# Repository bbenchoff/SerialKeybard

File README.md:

# Serial Keyboard

It's a keyboard that transmits serial. Or it's a 256-key keyboard, using 18 keys. Something like that. The main thing is that it transmits any serial byte.

## Notice

This repo contains a few files, but is mostly geared towards an unoptimized build with the internal structure consisting of five(!) different PCBs. The SerialKeyboard.brd is just a 18-key keyboard with diodes. The DisplayCarrier.brd is an interposer between the display and Motherboard.brd, which is the only thing with active electronics. There's also an Arduino in there and the front panel, which makes for a grand total of five different PCBs in this project.

I have started work on a simplified version, MasterBoard.brd, which would combine this all into one single circuit board. This work is not completed.

If someone can find me a source of 2U 'Transmit' keycaps, I'll get right on that.

Oh yeah, I noticed this repo was named 'SerialKeybard', but it's too late to fix it now.

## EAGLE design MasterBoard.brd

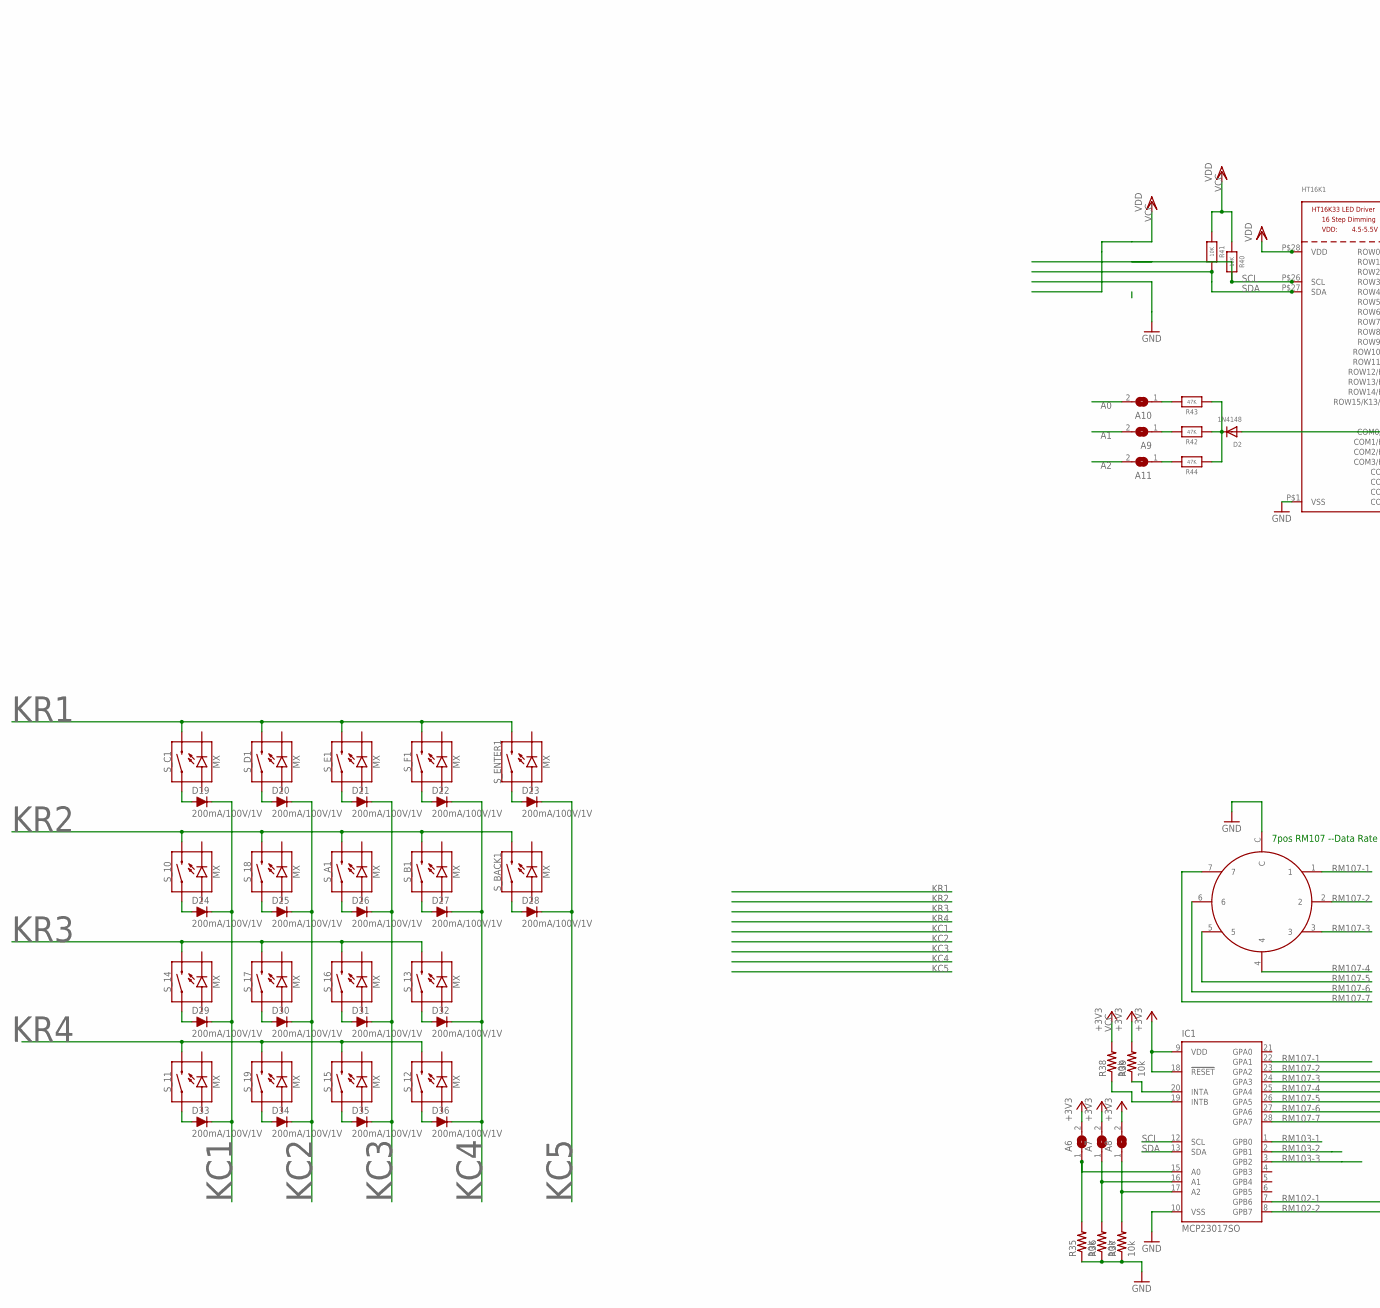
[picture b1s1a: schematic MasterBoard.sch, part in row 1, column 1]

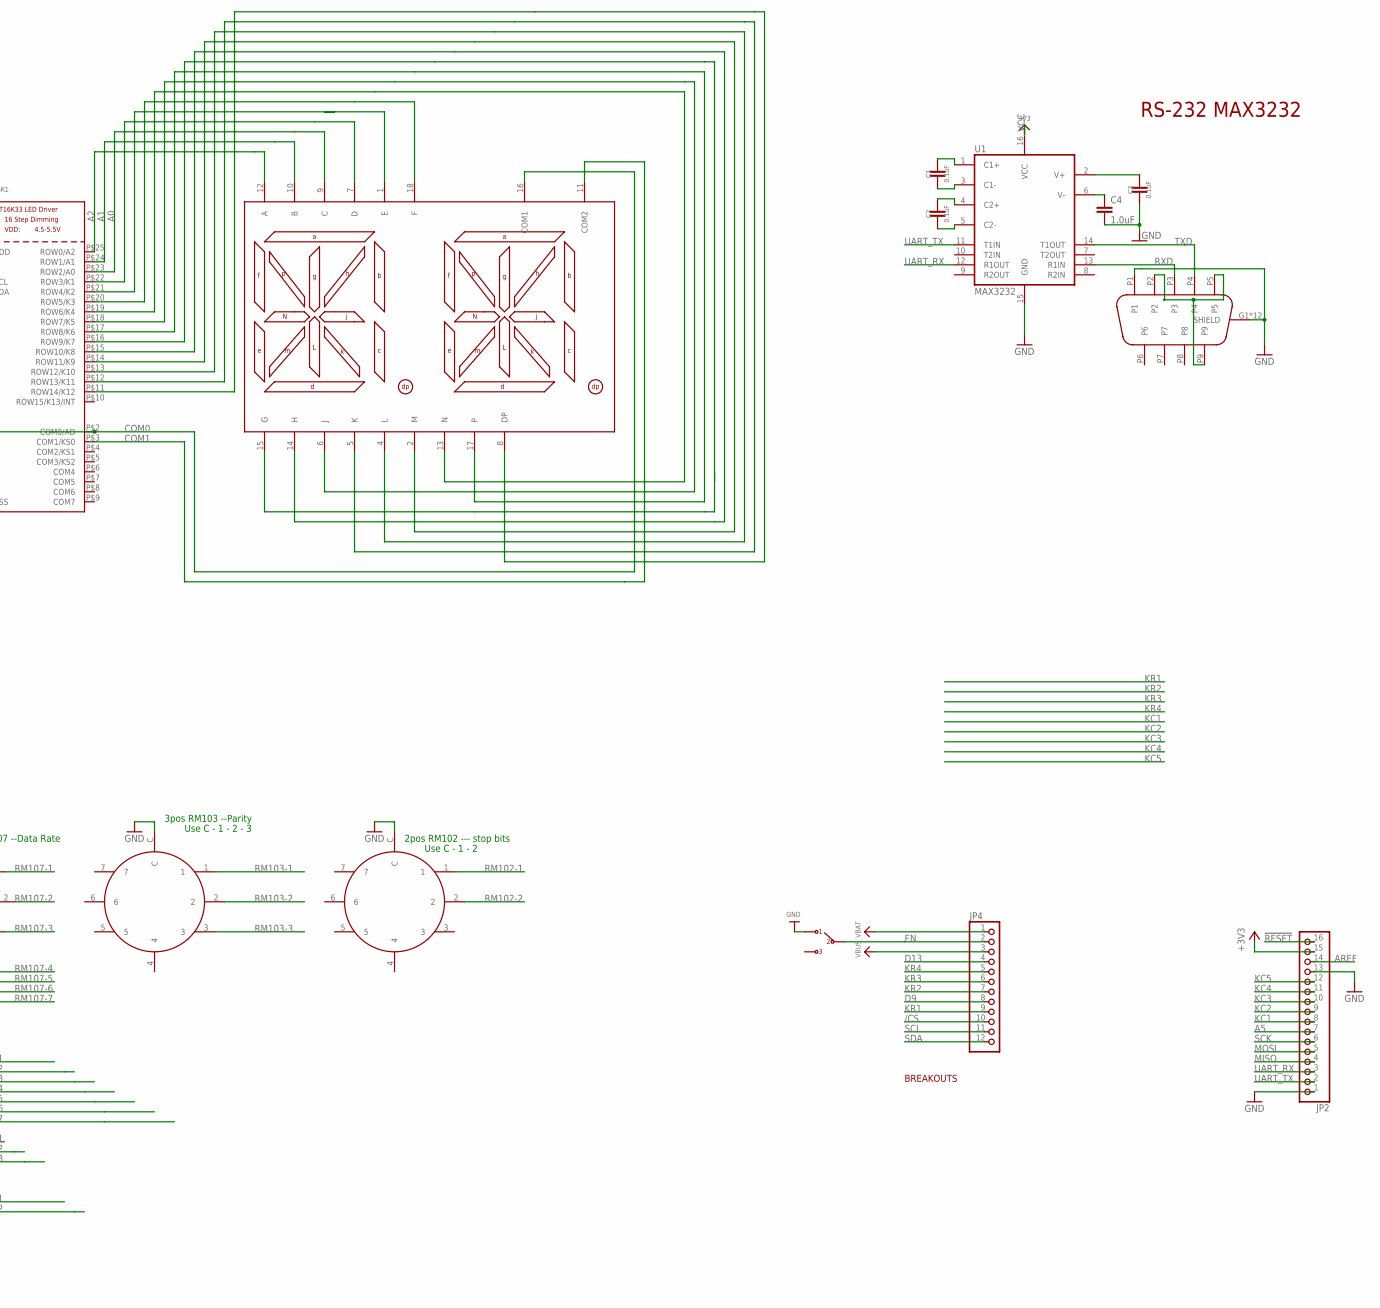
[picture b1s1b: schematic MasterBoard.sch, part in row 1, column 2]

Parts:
A6, A7, A8: SJ
A9, A10, A11: SOLDERJUMPERREFLOW_NOPASTE; SOLDERJUMPER_REFLOW_NOPASTE
C1, C2, C3: 0.1uF; 0805
C4: 1.0uF; 0805
D2: 1N4148; SOD-323F
D19, D20, D21, D22, D23, D24, D25, D26, D27, D28, D29, D30, D31, D32, D33, D34, D35, D36: 200mA/100V/1V; DIODE-1N4148
DE9FEMALE1: EDGEMOUNTDE9; DE09S065TLF
HT16K1: HT16K33_SOP28_SKINNY; SOP28_300MIL_SKINNY
IC1: MCP23017SO; SO28W
JP2: HEADER-1X16ROUND; 1X16_ROUND
JP4: HEADER-1X12; 1X12_ROUND
R35, R36, R37, R38, R39: 10k; M0805
R40, R41: 10K; 0805-NO
R42, R43, R44: 47K; 0805-NO
S_10, S_11, S_12, S_13, S_14, S_15, S_16, S_17, S_18, S_19: MX; CHERRY-MX-LED
S_A1: MX; CHERRY-MX-LED
S_B1: MX; CHERRY-MX-LED
S_BACK1: MX; CHERRY-MX-LED
S_C1: MX; CHERRY-MX-LED
S_D1: MX; CHERRY-MX-LED
S_E1: MX; CHERRY-MX-LED
S_ENTER1: MX; CHERRY-MX-LED
S_F1: MX; CHERRY-MX-LED
U1: MAX3232; SO16
U$11: BIG14SEG; HDSP
U$12, U$17, U$18: RM107772BCB
U$15: OS102011MA1QN1

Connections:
!RESET: JP2.16
/CS: JP4.10
A0: A10.2, HT16K1.P$23 (ROW2/A0), U$11.9 (C)
A1: A9.2, HT16K1.P$24 (ROW1/A1), U$11.10 (B)
A2: A11.2, HT16K1.P$25 (ROW0/A2), U$11.12 (A)
A5: JP2.7
AREF: JP2.14
COM0: D2.A, HT16K1.P$2 (COM0/AD), U$11.16 (COM1)
COM1: HT16K1.P$3 (COM1/KS0), U$11.11 (COM2)
D9: JP4.8
D13: JP4.4
EN: JP4.2, U$15.P$2
GND: C3.2, C4.2, DE9FEMALE1.G1 (SHIELD), DE9FEMALE1.G2 (SHIELD), DE9FEMALE1.G3 (SHIELD), DE9FEMALE1.G4 (SHIELD), DE9FEMALE1.G5 (SHIELD), DE9FEMALE1.G6 (SHIELD), DE9FEMALE1.G7 (SHIELD), DE9FEMALE1.G8 (SHIELD), DE9FEMALE1.G9 (SHIELD), DE9FEMALE1.G10 (SHIELD), DE9FEMALE1.G11 (SHIELD), DE9FEMALE1.G12 (SHIELD), DE9FEMALE1.P1, HT16K1.P$1 (VSS), IC1.10 (VSS), JP2.1, JP2.13, R35.1, R36.1, R37.1, U1.15 (GND), U$12.C, U$15.P$1, U$17.C, U$18.C
KC1: D19.C, D24.C, D29.C, D33.C, JP2.8
KC2: D20.C, D25.C, D30.C, D34.C, JP2.9
KC3: D21.C, D26.C, D31.C, D35.C, JP2.10
KC4: D22.C, D27.C, D32.C, D36.C, JP2.11
KC5: D23.C, D28.C, JP2.12
KR1: JP4.9, S_C1.S2 (2), S_D1.S2 (2), S_E1.S2 (2), S_ENTER1.S2 (2), S_F1.S2 (2)
KR2: JP4.7, S_10.S2 (2), S_18.S2 (2), S_A1.S2 (2), S_B1.S2 (2), S_BACK1.S2 (2)
KR3: JP4.6, S_13.S2 (2), S_14.S2 (2), S_16.S2 (2), S_17.S2 (2)
KR4: JP4.5, S_11.S2 (2), S_12.S2 (2), S_15.S2 (2), S_19.S2 (2)
MISO: JP2.4
MOSI: JP2.5
unnamed: D33.A, S_11.S1 (1)
unnamed: D34.A, S_19.S1 (1)
unnamed: D35.A, S_15.S1 (1)
unnamed: D36.A, S_12.S1 (1)
unnamed: D29.A, S_14.S1 (1)
unnamed: D30.A, S_17.S1 (1)
unnamed: D31.A, S_16.S1 (1)
unnamed: D32.A, S_13.S1 (1)
unnamed: D24.A, S_10.S1 (1)
unnamed: D25.A, S_18.S1 (1)
unnamed: D26.A, S_A1.S1 (1)
unnamed: D27.A, S_B1.S1 (1)
unnamed: D28.A, S_BACK1.S1 (1)
unnamed: D23.A, S_ENTER1.S1 (1)
unnamed: D22.A, S_F1.S1 (1)
unnamed: D21.A, S_E1.S1 (1)
unnamed: D20.A, S_D1.S1 (1)
unnamed: D19.A, S_C1.S1 (1)
unnamed: C1.2, U1.3 (C1-)
unnamed: C1.1, U1.1 (C1+)
unnamed: C2.1, U1.4 (C2+)
unnamed: C2.2, U1.5 (C2-)
unnamed: C3.1, U1.2 (V+)
unnamed: C4.1, U1.6 (V-)
unnamed: DE9FEMALE1.P2, DE9FEMALE1.P5, DE9FEMALE1.P9
unnamed: A6.1, IC1.15 (A0), R35.2
unnamed: A7.1, IC1.16 (A1), R36.2
unnamed: A8.1, IC1.17 (A2), R37.2
unnamed: IC1.19 (INTB), R38.1
unnamed: IC1.20 (INTA), R39.1
unnamed: A9.1, R42.2
unnamed: A10.1, R43.2
unnamed: HT16K1.P$22 (ROW3/K1), U$11.7 (D)
unnamed: HT16K1.P$21 (ROW4/K2), U$11.1 (E)
unnamed: HT16K1.P$20 (ROW5/K3), U$11.18 (F)
unnamed: HT16K1.P$19 (ROW6/K4), U$11.13 (N)
unnamed: HT16K1.P$18 (ROW7/K5), U$11.6 (J)
unnamed: D2.C, R42.1, R43.1, R44.1
unnamed: A11.1, R44.2
unnamed: HT16K1.P$17 (ROW8/K6), U$11.17
unnamed: HT16K1.P$16 (ROW9/K7), U$11.15 (G)
unnamed: HT16K1.P$15 (ROW10/K8), U$11.14 (H)
unnamed: HT16K1.P$14 (ROW11/K9), U$11.2 (M)
unnamed: HT16K1.P$13 (ROW12/K10), U$11.4 (L)
unnamed: HT16K1.P$12 (ROW13/K11), U$11.5 (K)
unnamed: HT16K1.P$11 (ROW14/K12), U$11.8 (DP)
RM102-1: IC1.7 (GPB6), U$18.1
RM102-2: IC1.8 (GPB7), U$18.2
RM103-1: IC1.1 (GPB0), U$17.1
RM103-2: IC1.2 (GPB1), U$17.2
RM103-3: IC1.3 (GPB2), U$17.3
RM107-1: IC1.22 (GPA1), U$12.1
RM107-2: IC1.23 (GPA2), U$12.2
RM107-3: IC1.24 (GPA3), U$12.3
RM107-4: IC1.25 (GPA4), U$12.4
RM107-5: IC1.26 (GPA5), U$12.5
RM107-6: IC1.27 (GPA6), U$12.6
RM107-7: IC1.28 (GPA7), U$12.7
RXD: DE9FEMALE1.P3, U1.13 (R1IN)
SCK: JP2.6
SCL: HT16K1.P$26 (SCL), IC1.12 (SCL), JP4.11, R40.2
SDA: HT16K1.P$27 (SDA), IC1.13 (SDA), JP4.12, R41.2
TXD: DE9FEMALE1.P4, U1.14 (T1OUT)
UART_RX: JP2.3, U1.12 (R1OUT)
UART_TX: JP2.2, U1.11 (T1IN)
VBAT: JP4.1
VBUS: JP4.3
VCC: A6.2, A7.2, A8.2, HT16K1.P$28 (VDD), IC1.9 (VDD), IC1.18 (!RESET), JP2.15, R38.2, R39.2, R40.1, R41.1, U1.16 (VCC)

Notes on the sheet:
RS-232 MAX3232
7pos RM107 --Data Rate
3pos RM103 --Parity
Use C - 1 - 2 - 3
2pos RM102 --- stop bits
Use C - 1 - 2
BREAKOUTS

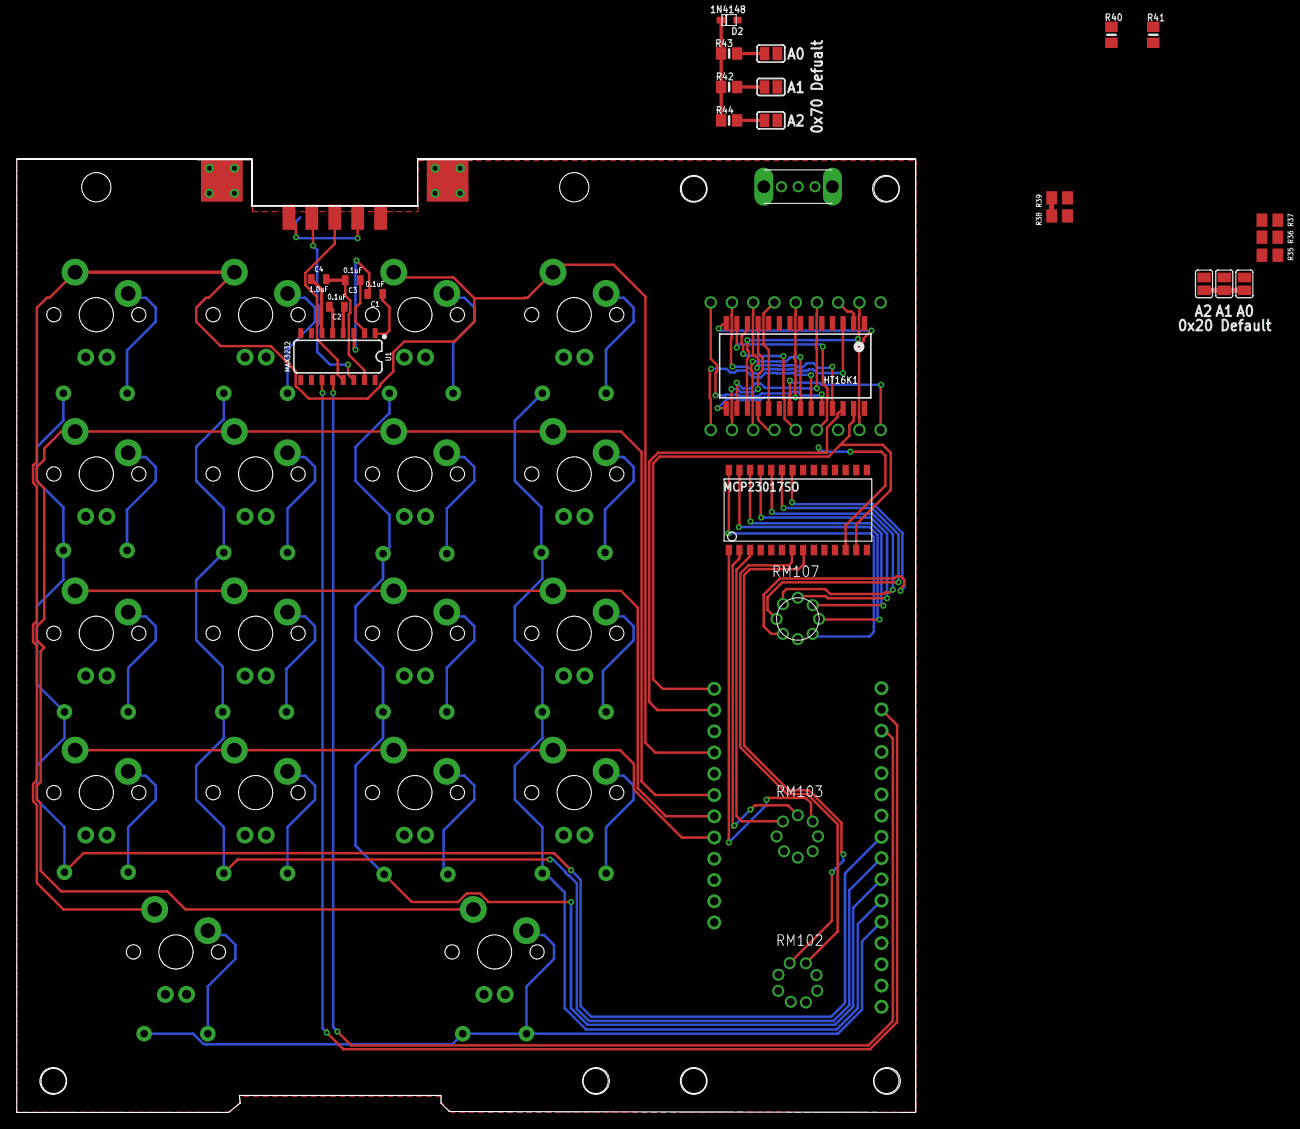
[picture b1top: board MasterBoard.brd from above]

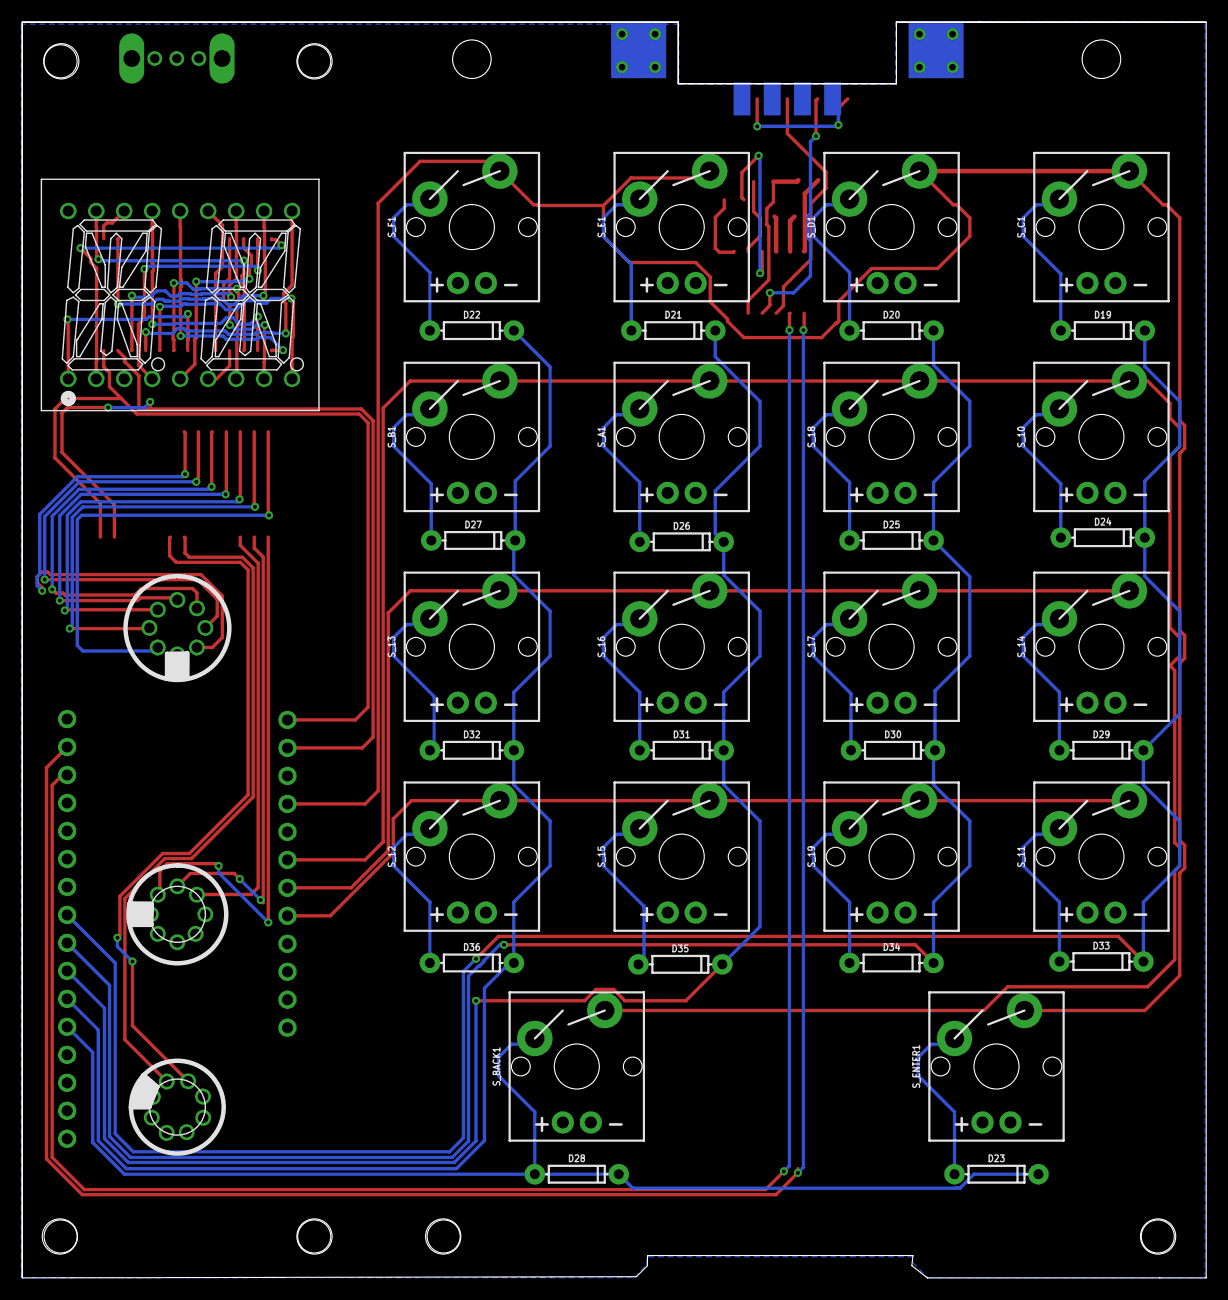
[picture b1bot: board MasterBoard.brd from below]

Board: 2 copper layers, 107.5 x 114.0 mm, 68 parts (39 on the bottom side), 81 nets.

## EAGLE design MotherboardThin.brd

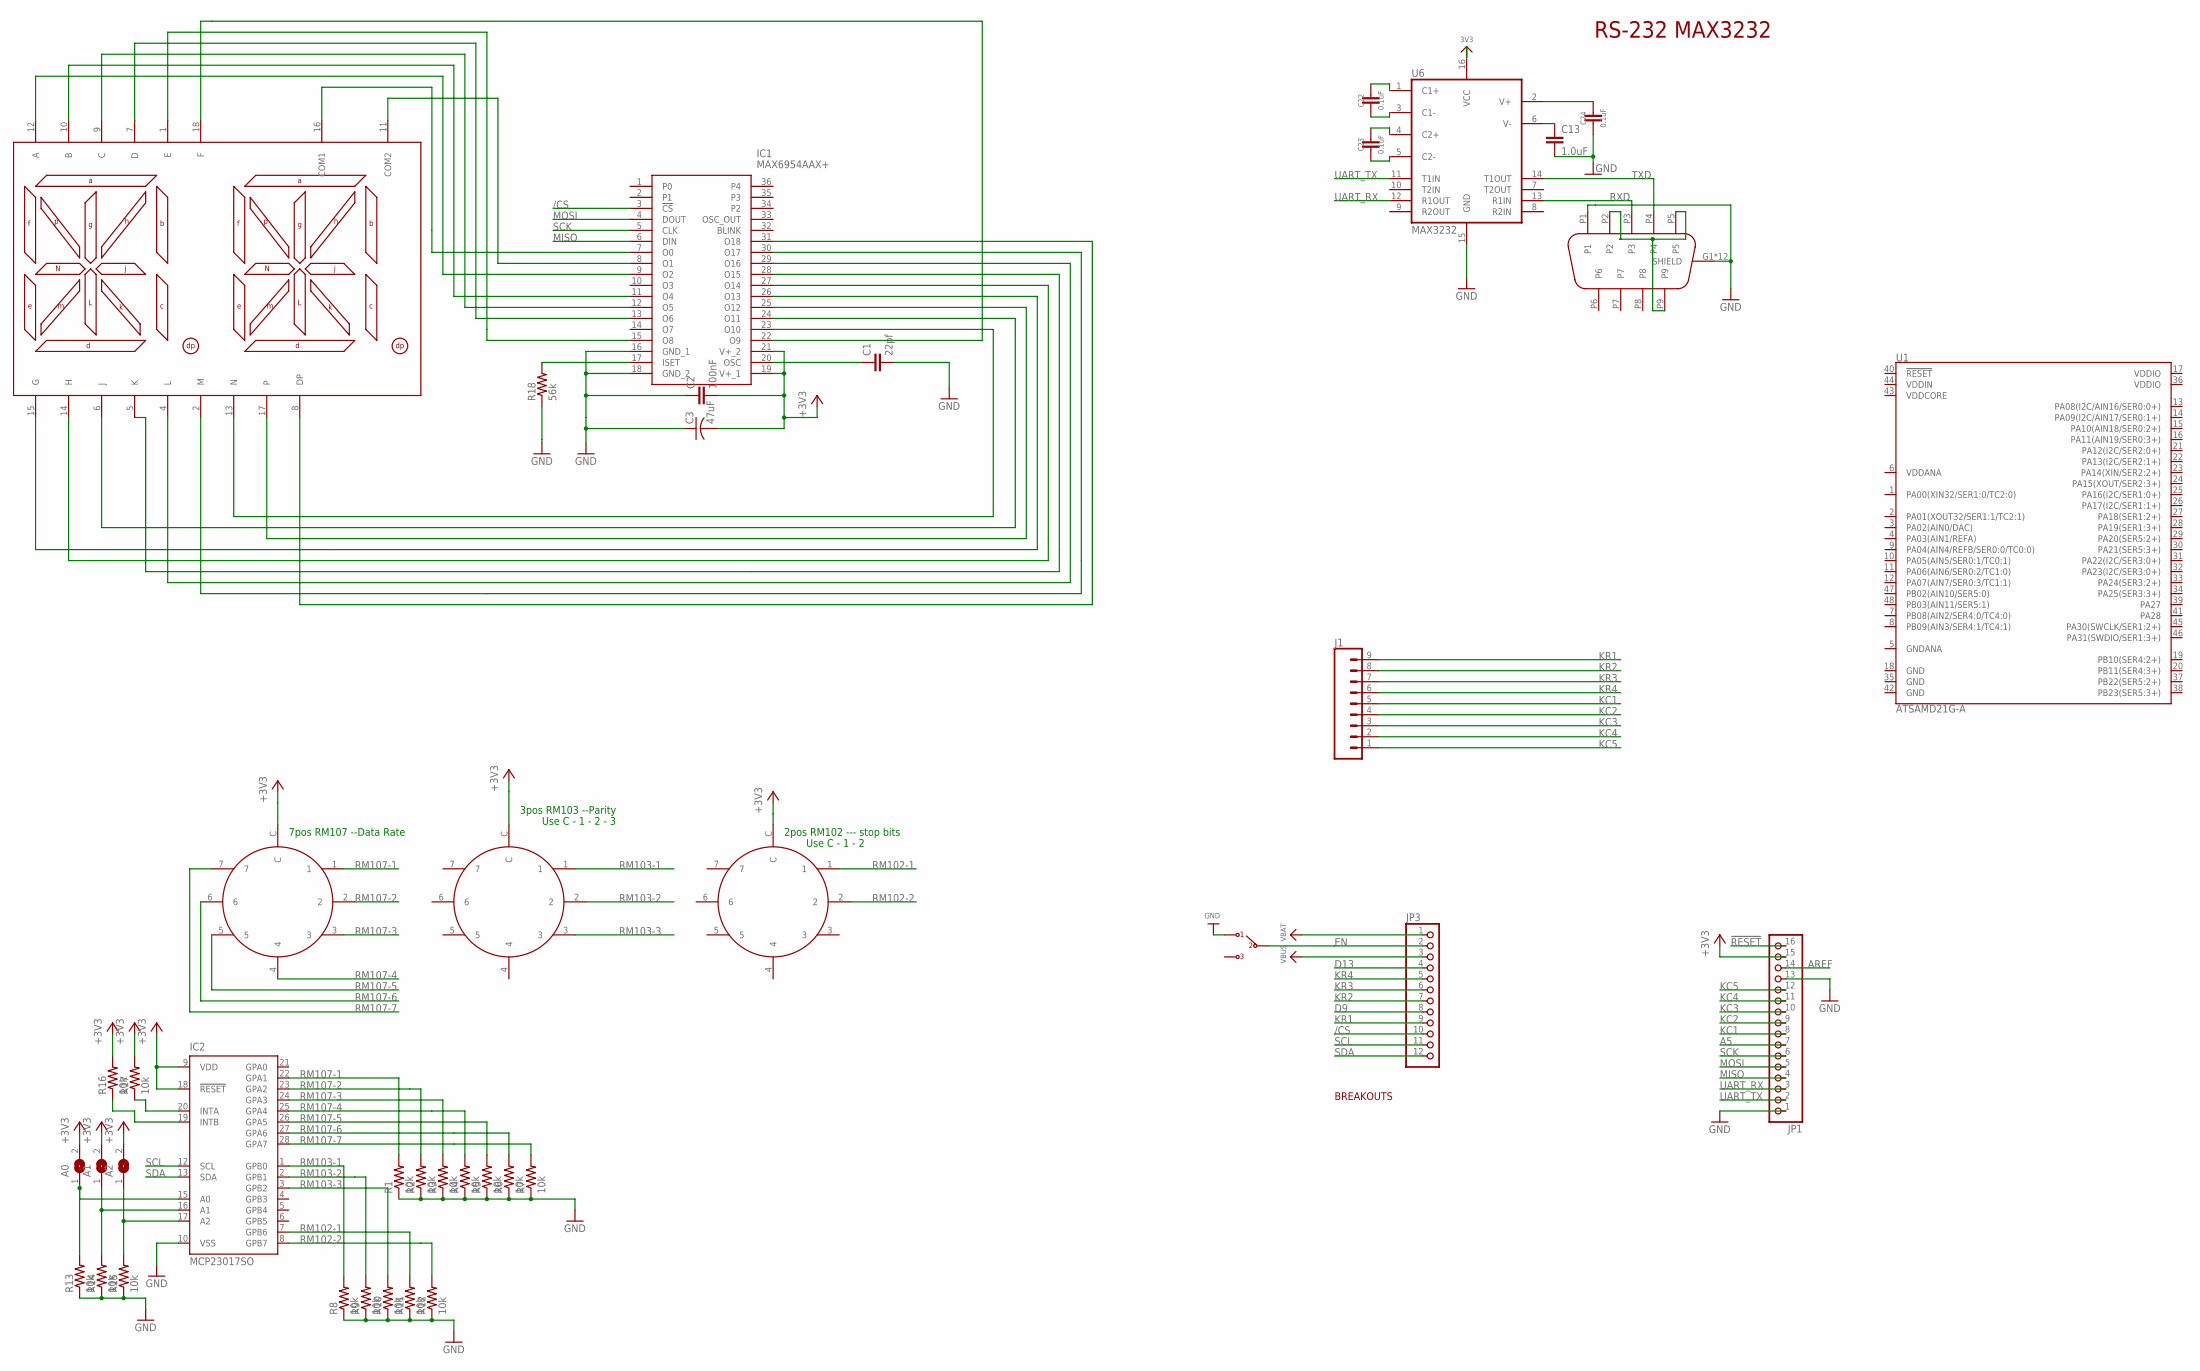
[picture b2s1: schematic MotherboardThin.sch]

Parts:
A0, A1, A2: SJ
C1: 22pf; 0805
C2: 100nF; 0805
C3: 47uF; C1206
C13: 1.0uF; 0805
C22, C23, C24: 0.1uF; 0805
DE9FEMALE: EDGEMOUNTDE9; DE09S065TLF
IC1: MAX6954AAX+; SOP80P1030X264-36N
IC2: MCP23017SO; SO28W
J1: CONN_09; 1X09
JP1: HEADER-1X16ROUND; 1X16_ROUND
JP3: HEADER-1X12; 1X12_ROUND
R1, R2, R3, R4, R5, R6, R7, R8, R9, R10, R11, R12, R13, R14, R15, R16, R17: 10k; M0805
R18: 56k; M0805
U1: ATSAMD21G-A; TQFP-48
U6: MAX3232; SO16
U$1: HDSP-A27C; DIP-18
U$2, U$3, U$6: RM107772BCB
U$5: OS102011MA1QN1

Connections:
3V3: U6.16 (VCC)
!RESET: JP1.16
+3V3: A0.2, A1.2, A2.2, C2.2, C3.2, IC1.19 (V+_1), IC1.21 (V+_2), IC2.9 (VDD), IC2.18 (!RESET), JP1.15, R16.2, R17.2, U$2.C, U$3.C, U$6.C
/CS: IC1.3 (!CS), JP3.10
A5: JP1.7
AREF: JP1.14
D9: JP3.8
D13: JP3.4
EN: JP3.2, U$5.P$2
GND: C1.2, C2.1, C3.1, C13.2, C24.2, DE9FEMALE.G1 (SHIELD), DE9FEMALE.G2 (SHIELD), DE9FEMALE.G3 (SHIELD), DE9FEMALE.G4 (SHIELD), DE9FEMALE.G5 (SHIELD), DE9FEMALE.G6 (SHIELD), DE9FEMALE.G7 (SHIELD), DE9FEMALE.G8 (SHIELD), DE9FEMALE.G9 (SHIELD), DE9FEMALE.G10 (SHIELD), DE9FEMALE.G11 (SHIELD), DE9FEMALE.G12 (SHIELD), DE9FEMALE.P1, IC1.16 (GND_1), IC1.18 (GND_2), IC2.10 (VSS), JP1.1, JP1.13, R1.1, R2.1, R3.1, R4.1, R5.1, R6.1, R7.1, R8.1, R9.1, R10.1, R11.1, R12.1, R13.1, R14.1, R15.1, R18.1, U6.15 (GND), U$5.P$1
KC1: J1.5, JP1.8
KC2: J1.4, JP1.9
KC3: J1.3, JP1.10
KC4: J1.2, JP1.11
KC5: J1.1, JP1.12
KR1: J1.9, JP3.9
KR2: J1.8, JP3.7
KR3: J1.7, JP3.6
KR4: J1.6, JP3.5
MISO: IC1.6 (DIN), JP1.4
MOSI: IC1.4 (DOUT), JP1.5
unnamed: IC1.7 (O0), U$1.16 (COM1)
unnamed: IC1.9 (O2), U$1.12 (A)
unnamed: IC1.11 (O4), U$1.10 (B)
unnamed: IC1.12 (O5), U$1.9 (C)
unnamed: IC1.13 (O6), U$1.7 (D)
unnamed: IC1.15 (O8), U$1.1 (E)
unnamed: IC1.22 (O9), U$1.18 (F)
unnamed: IC1.23 (O10), U$1.13 (N)
unnamed: IC1.24 (O11), U$1.6 (J)
unnamed: IC1.25 (O12), U$1.17
unnamed: IC1.26 (O13), U$1.15 (G)
unnamed: IC1.27 (O14), U$1.14 (H)
unnamed: IC1.28 (O15), U$1.5 (K)
unnamed: IC1.29 (O16), U$1.4 (L)
unnamed: IC1.30 (O17), U$1.2 (M)
unnamed: IC1.31 (O18), U$1.8 (DP)
unnamed: IC1.8 (O1), U$1.11 (COM2)
unnamed: C22.2, U6.3 (C1-)
unnamed: C22.1, U6.1 (C1+)
unnamed: C23.1, U6.4 (C2+)
unnamed: C23.2, U6.5 (C2-)
unnamed: C24.1, U6.2 (V+)
unnamed: C13.1, U6.6 (V-)
unnamed: DE9FEMALE.P2, DE9FEMALE.P5, DE9FEMALE.P9
unnamed: A0.1, IC2.15 (A0), R13.2
unnamed: A1.1, IC2.16 (A1), R14.2
unnamed: A2.1, IC2.17 (A2), R15.2
unnamed: IC2.19 (INTB), R16.1
unnamed: IC2.20 (INTA), R17.1
unnamed: C1.1, IC1.20 (OSC)
unnamed: IC1.17 (ISET), R18.2
RM102-1: IC2.7 (GPB6), R11.2, U$6.1
RM102-2: IC2.8 (GPB7), R12.2, U$6.2
RM103-1: IC2.1 (GPB0), R8.2, U$3.1
RM103-2: IC2.2 (GPB1), R9.2, U$3.2
RM103-3: IC2.3 (GPB2), R10.2, U$3.3
RM107-1: IC2.22 (GPA1), R1.2, U$2.1
RM107-2: IC2.23 (GPA2), R2.2, U$2.2
RM107-3: IC2.24 (GPA3), R3.2, U$2.3
RM107-4: IC2.25 (GPA4), R4.2, U$2.4
RM107-5: IC2.26 (GPA5), R5.2, U$2.5
RM107-6: IC2.27 (GPA6), R6.2, U$2.6
RM107-7: IC2.28 (GPA7), R7.2, U$2.7
RXD: DE9FEMALE.P3, U6.13 (R1IN)
SCK: IC1.5 (CLK), JP1.6
SCL: IC2.12 (SCL), JP3.11
SDA: IC2.13 (SDA), JP3.12
TXD: DE9FEMALE.P4, U6.14 (T1OUT)
UART_RX: JP1.3, U6.12 (R1OUT)
UART_TX: JP1.2, U6.11 (T1IN)
VBAT: JP3.1
VBUS: JP3.3

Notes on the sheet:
RS-232 MAX3232
7pos RM107 --Data Rate
3pos RM103 --Parity
Use C - 1 - 2 - 3
2pos RM102 --- stop bits
Use C - 1 - 2
BREAKOUTS

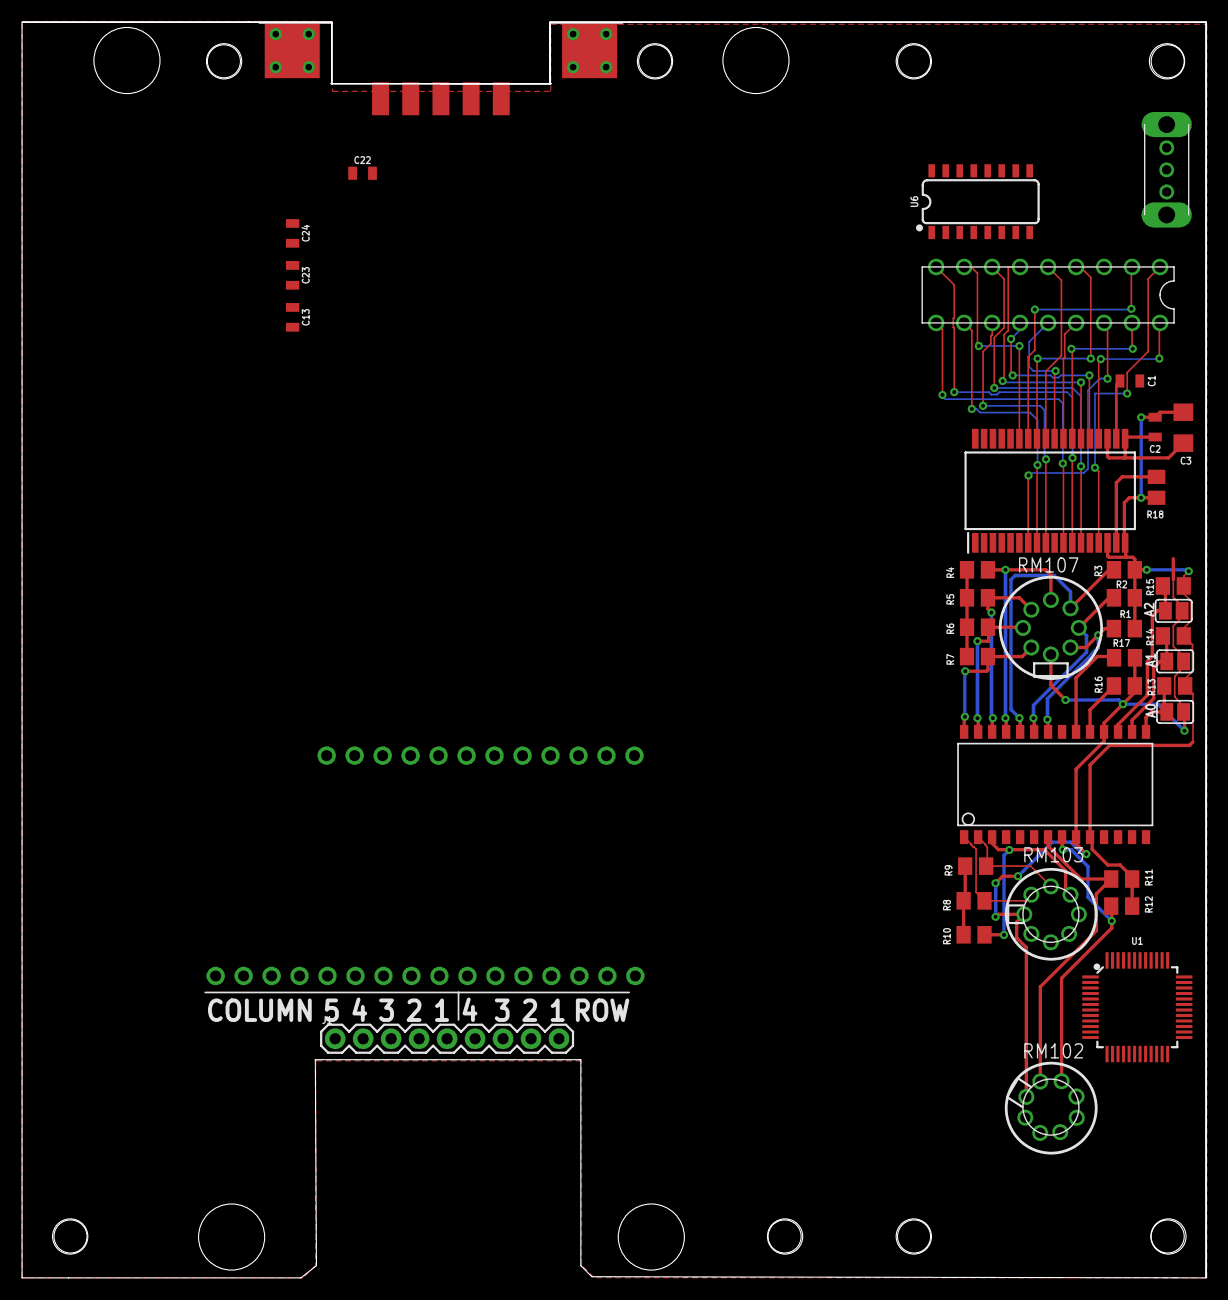
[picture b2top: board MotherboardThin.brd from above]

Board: 2 copper layers, 107.5 x 114.0 mm, 41 parts (1 on the bottom side), 65 nets.

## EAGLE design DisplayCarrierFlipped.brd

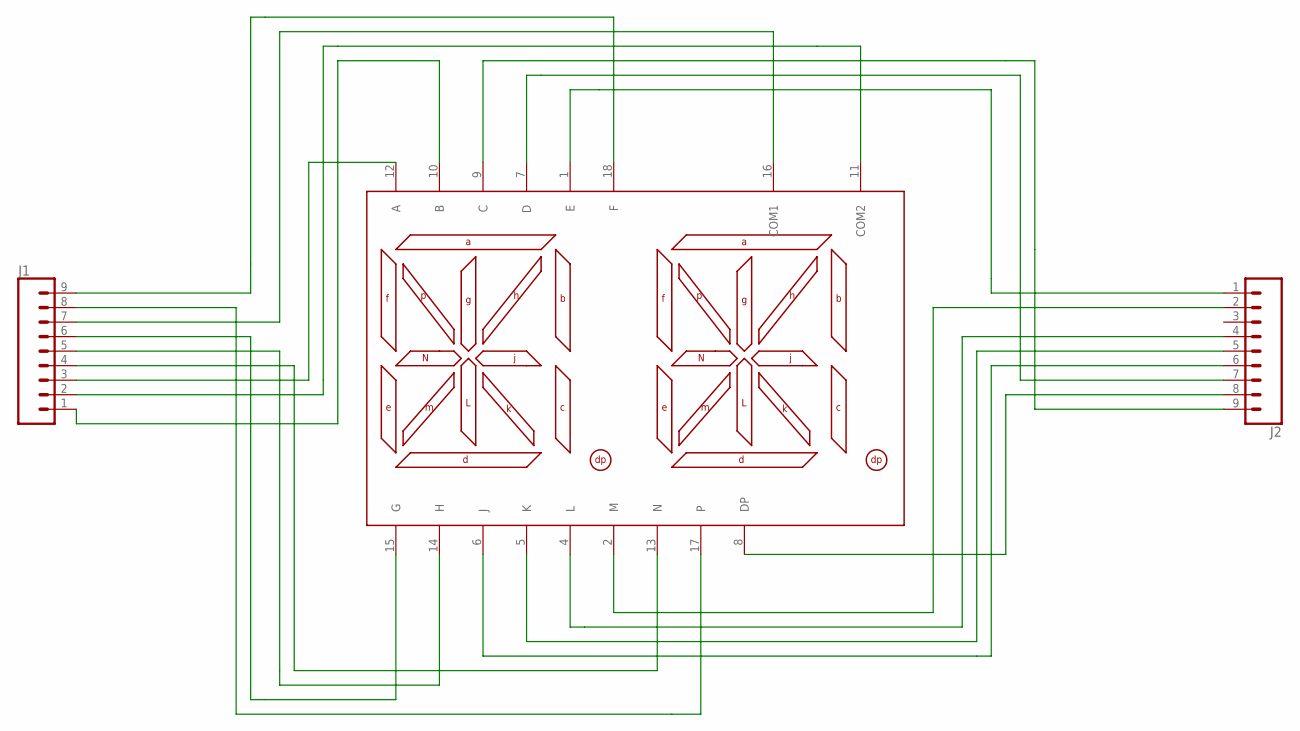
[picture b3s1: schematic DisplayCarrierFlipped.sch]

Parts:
J1, J2: CONN_09; 1X09
U$1: HDSP-A27C; DIP-18

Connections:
unnamed: J2.1, U$1.1 (E)
unnamed: J1.1, U$1.10 (B)
unnamed: J1.2, U$1.11 (COM2)
unnamed: J1.3, U$1.12 (A)
unnamed: J1.4, U$1.13 (N)
unnamed: J1.5, U$1.14 (H)
unnamed: J1.6, U$1.15 (G)
unnamed: J1.7, U$1.16 (COM1)
unnamed: J1.8, U$1.17
unnamed: J2.2, U$1.2 (M)
unnamed: J2.4, U$1.4 (L)
unnamed: J2.5, U$1.5 (K)
unnamed: J2.6, U$1.6 (J)
unnamed: J2.7, U$1.7 (D)
unnamed: J2.8, U$1.8 (DP)
unnamed: J1.9, U$1.18 (F)
unnamed: J2.9, U$1.9 (C)

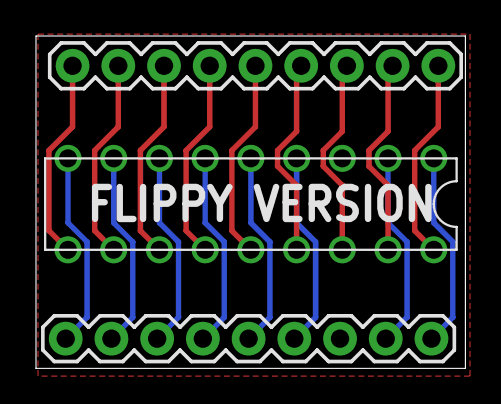
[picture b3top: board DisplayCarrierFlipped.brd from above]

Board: 2 copper layers, 23.9 x 18.5 mm, 3 parts (0 on the bottom side), 17 nets.

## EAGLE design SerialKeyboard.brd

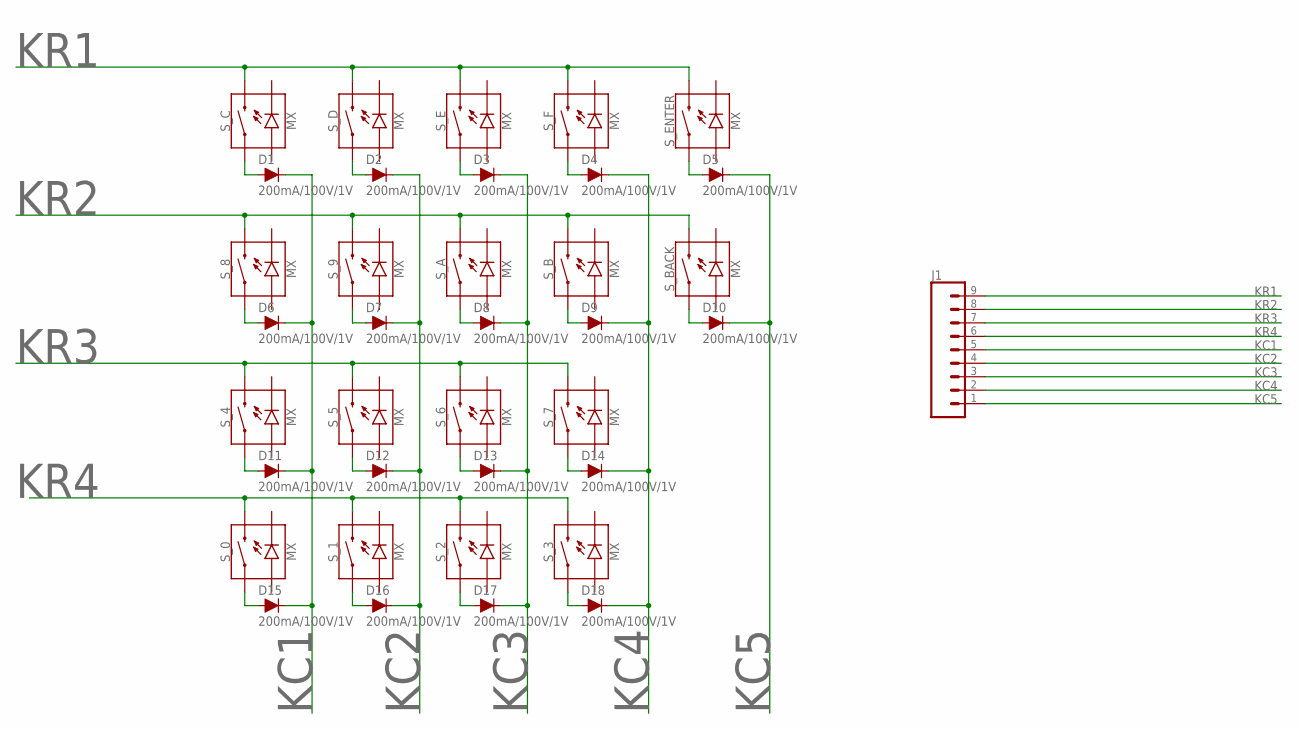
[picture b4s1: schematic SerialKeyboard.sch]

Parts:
D1, D2, D3, D4, D5, D6, D7, D8, D9, D10, D11, D12, D13, D14, D15, D16, D17, D18: 200mA/100V/1V; DIODE-1N4148
J1: CONN_09; 1X09
S_0, S_1, S_2, S_3, S_4, S_5, S_6, S_7, S_8, S_9: MX; CHERRY-MX-LED
S_A: MX; CHERRY-MX-LED
S_B: MX; CHERRY-MX-LED
S_BACK: MX; CHERRY-MX-LED
S_C: MX; CHERRY-MX-LED
S_D: MX; CHERRY-MX-LED
S_E: MX; CHERRY-MX-LED
S_ENTER: MX; CHERRY-MX-LED
S_F: MX; CHERRY-MX-LED

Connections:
KC1: D1.C, D6.C, D11.C, D15.C, J1.5
KC2: D2.C, D7.C, D12.C, D16.C, J1.4
KC3: D3.C, D8.C, D13.C, D17.C, J1.3
KC4: D4.C, D9.C, D14.C, D18.C, J1.2
KC5: D5.C, D10.C, J1.1
KR1: J1.9, S_C.S2 (2), S_D.S2 (2), S_E.S2 (2), S_ENTER.S2 (2), S_F.S2 (2)
KR2: J1.8, S_8.S2 (2), S_9.S2 (2), S_A.S2 (2), S_B.S2 (2), S_BACK.S2 (2)
KR3: J1.7, S_4.S2 (2), S_5.S2 (2), S_6.S2 (2), S_7.S2 (2)
KR4: J1.6, S_0.S2 (2), S_1.S2 (2), S_2.S2 (2), S_3.S2 (2)
unnamed: D15.A, S_0.S1 (1)
unnamed: D16.A, S_1.S1 (1)
unnamed: D17.A, S_2.S1 (1)
unnamed: D18.A, S_3.S1 (1)
unnamed: D11.A, S_4.S1 (1)
unnamed: D12.A, S_5.S1 (1)
unnamed: D13.A, S_6.S1 (1)
unnamed: D14.A, S_7.S1 (1)
unnamed: D6.A, S_8.S1 (1)
unnamed: D7.A, S_9.S1 (1)
unnamed: D8.A, S_A.S1 (1)
unnamed: D9.A, S_B.S1 (1)
unnamed: D10.A, S_BACK.S1 (1)
unnamed: D5.A, S_ENTER.S1 (1)
unnamed: D4.A, S_F.S1 (1)
unnamed: D3.A, S_E.S1 (1)
unnamed: D2.A, S_D.S1 (1)
unnamed: D1.A, S_C.S1 (1)

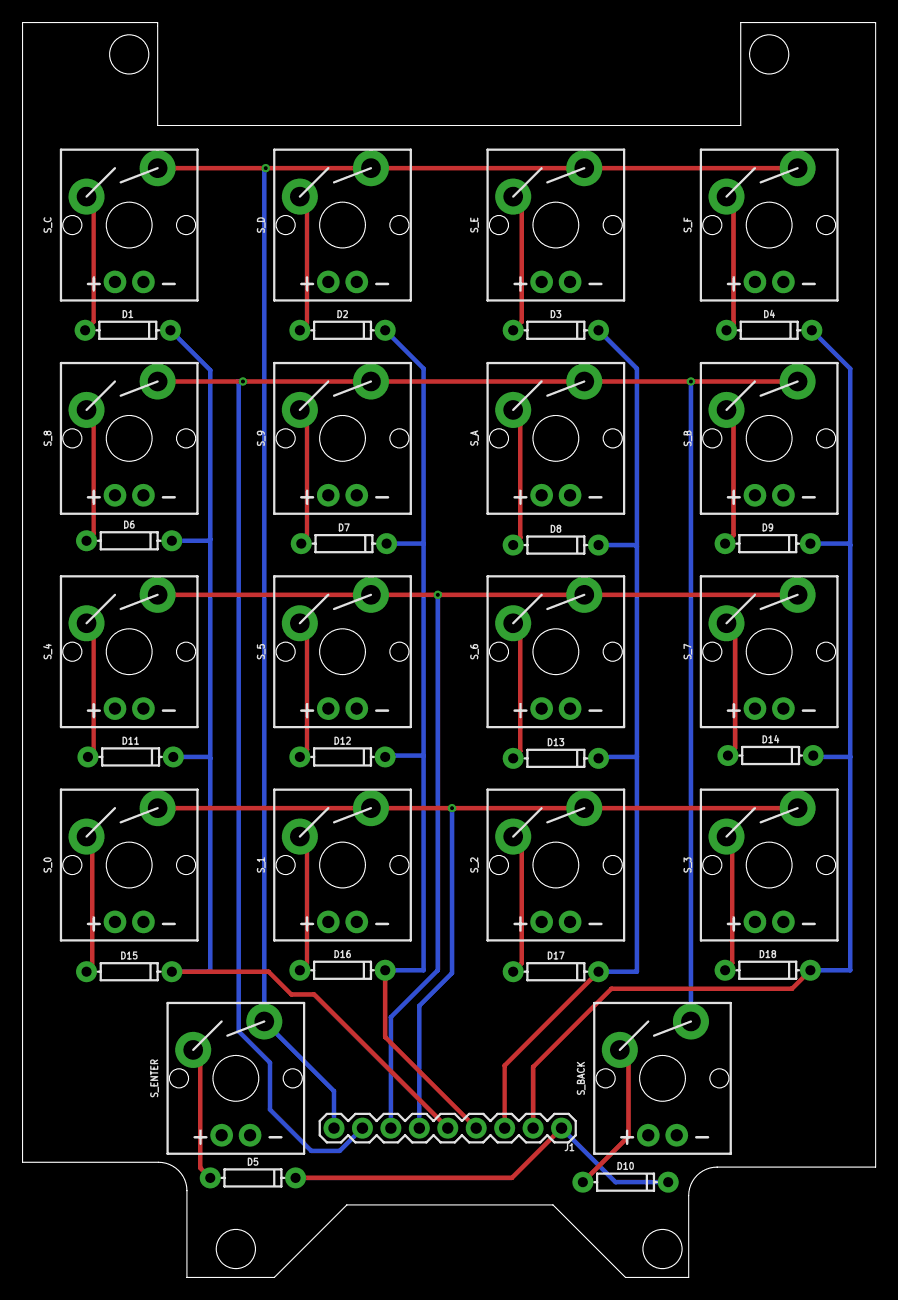
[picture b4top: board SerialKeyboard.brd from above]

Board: 2 copper layers, 76.2 x 112.1 mm, 37 parts (0 on the bottom side), 27 nets.

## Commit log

2020-12-28 I think I got this taken care of
2021-02-01 well it works now
2021-02-01 added the IO expander code
2021-03-12 Added renders, readme, cleanup

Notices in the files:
parts and their libraries:
SparkFun-Connectors: Licensing: Creative Commons ShareAlike 4.0 International - https://creativecommons.org/licenses/by-sa/4.0
microbuilder: This work is placed in the public domain, and may be freely used for commercial and non-commercial work with the following conditions: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
